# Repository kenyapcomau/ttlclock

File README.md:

# TTL clock

These are the Kicad design files for the TTL clock described in my [Hackaday project](https://hackaday.io/project/168157-ttl-binary-clock)

## Versioning

First release November 2019

## Notes

Due to the 2 LS load fan out of the CD4060 (U8), you should use a 74LS50 (U12) and not a standard TTL package, otherwise the 1 Hz signal will be unreliable. Anyway non-LS parts are rare these days. LS is lower power consumption too.

## Authors

* **Ken Yap**

## License

See the [LICENSE](LICENSE.md) file for license rights and limitations (MIT).

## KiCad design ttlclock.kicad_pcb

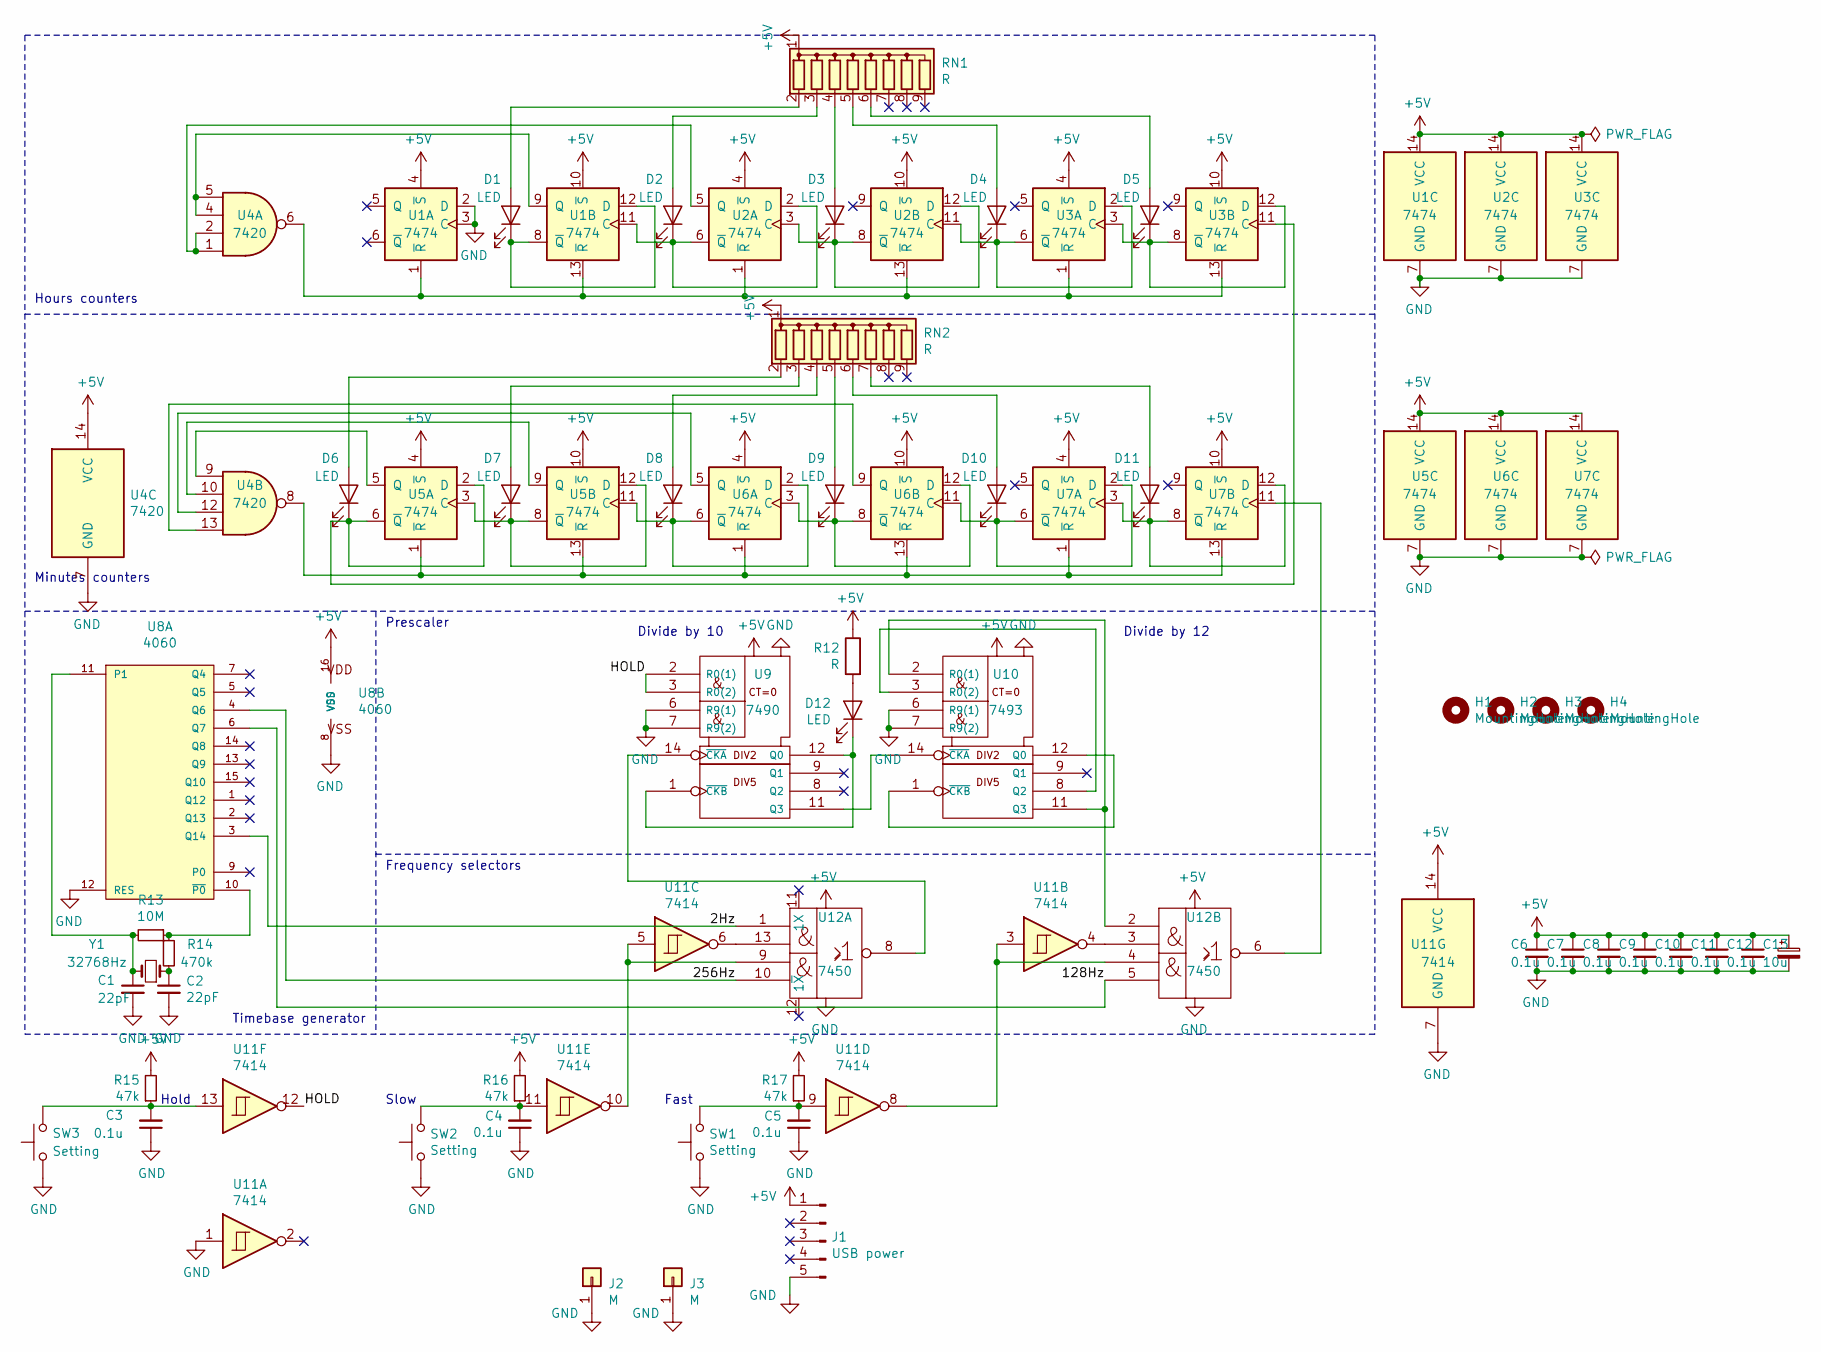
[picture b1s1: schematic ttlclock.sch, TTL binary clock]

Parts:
C1, C2: 22pF; C_Disc_D3.0mm_W1.6mm_P2.50mm
C3, C4, C5, C6, C7, C8, C9, C10, C11, C12: 0.1u; C_Rect_L7.2mm_W2.5mm_P5.00mm_FKS2_FKP2_MKS2_MKP2
C13: 10u; CP_Radial_D6.3mm_P2.50mm
D1, D2, D3, D4, D5, D6, D7, D8, D9, D10, D11, D12: LED; LED_D3.0mm
H1, H2, H3, H4: MountingHole; MountingHole_3.5mm_Pad
J1: USB power; PinHeader_1x05_P2.54mm_Vertical
J2, J3: M; PinHeader_1x01_P2.54mm_Vertical
R12: R; R_Axial_DIN0207_L6.3mm_D2.5mm_P10.16mm_Horizontal
R13: 10M; R_Axial_DIN0207_L6.3mm_D2.5mm_P10.16mm_Horizontal
R14: 470k; R_Axial_DIN0207_L6.3mm_D2.5mm_P10.16mm_Horizontal
R15, R16, R17: 47k; R_Axial_DIN0207_L6.3mm_D2.5mm_P10.16mm_Horizontal
RN1, RN2: R; R_Array_SIP9
SW1, SW2, SW3: Setting; SW_PUSH_6mm_H4.3mm
U1, U2, U3, U5, U6, U7: 7474; DIP-14_W7.62mm_LongPads
U4: 7420; DIP-14_W7.62mm_LongPads
U8: 4060; DIP-16_W7.62mm_LongPads
U9: 7490; DIP-14_W7.62mm_LongPads
U10: 7493; DIP-14_W7.62mm_LongPads
U11: 7414; DIP-14_W7.62mm_LongPads
U12: 7450; DIP-14_W7.62mm_LongPads
Y1: 32768Hz; Crystal_C38-LF_D3.0mm_L8.0mm_Horizontal

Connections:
+5V: C6.1, C7.1, C8.1, C9.1, C10.1, C11.1, C12.1, C13.1, J1.1, R12.1, R15.2, R16.2, R17.2, RN1.1 (common), RN2.1 (common), U1.4 (~S), U1.10 (~S), U1.14 (VCC), U2.4 (~S), U2.10 (~S), U2.14 (VCC), U3.4 (~S), U3.10 (~S), U3.14 (VCC), U4.14 (VCC), U5.4 (~S), U5.10 (~S), U5.14 (VCC), U6.4 (~S), U6.10 (~S), U6.14 (VCC), U7.4 (~S), U7.10 (~S), U7.14 (VCC), U8.16 (VDD), U9.5 (VCC), U10.5 (VCC), U11.14 (VCC), U12.14 (VCC)
/2Hz: U8.3 (Q14), U12.1
/128Hz: U8.6 (Q7), U12.5
/256Hz: U8.4 (Q6), U12.10
/HOLD: U9.2 (R0(1)), U9.3 (R0(2)), U11.12
GND: C1.2, C2.2, C3.1, C4.1, C5.1, C6.2, C7.2, C8.2, C9.2, C10.2, C11.2, C12.2, C13.2, J1.5, J2.1, J3.1, SW1.1, SW2.1, SW3.1, U1.2 (D), U1.3 (C), U1.7 (GND), U2.7 (GND), U3.7 (GND), U4.7 (GND), U5.7 (GND), U6.7 (GND), U7.7 (GND), U8.8 (VSS), U8.12 (RES), U9.6 (R9(1)), U9.7 (R9(2)), U9.10 (GND), U10.6 (R9(1)), U10.7 (R9(2)), U10.10 (GND), U11.1, U11.7 (GND), U12.7 (GND)
unnamed: C1.1, R13.2, U8.11 (P1), Y1.2
unnamed: C2.1, R14.2, Y1.1
unnamed: C3.2, R15.1, SW3.2, U11.13
unnamed: C4.2, R16.1, SW2.2, U11.11
unnamed: C5.2, R17.1, SW1.2, U11.9
unnamed: D1.1 (K), U1.8 (~Q), U1.12 (D)
unnamed: D1.2 (A), RN1.2 (R1)
unnamed: D2.1 (K), U1.11 (C), U2.2 (D), U2.6 (~Q)
unnamed: D2.2 (A), RN1.3 (R2)
unnamed: D3.1 (K), U2.3 (C), U2.8 (~Q), U2.12 (D)
unnamed: D3.2 (A), RN1.4 (R3)
unnamed: D4.1 (K), U2.11 (C), U3.2 (D), U3.6 (~Q)
unnamed: D4.2 (A), RN1.5 (R4)
unnamed: D5.1 (K), U3.3 (C), U3.8 (~Q), U3.12 (D)
unnamed: D5.2 (A), RN1.6 (R5)
unnamed: D6.1 (K), U3.11 (C), U5.2 (D), U5.6 (~Q)
unnamed: D6.2 (A), RN2.2 (R1)
unnamed: D7.1 (K), U5.3 (C), U5.8 (~Q), U5.12 (D)
unnamed: D7.2 (A), RN2.3 (R2)
unnamed: D8.1 (K), U5.11 (C), U6.2 (D), U6.6 (~Q)
unnamed: D8.2 (A), RN2.4 (R3)
unnamed: D9.1 (K), U6.3 (C), U6.8 (~Q), U6.12 (D)
unnamed: D9.2 (A), RN2.5 (R4)
unnamed: D10.1 (K), U6.11 (C), U7.2 (D), U7.6 (~Q)
unnamed: D10.2 (A), RN2.6 (R5)
unnamed: D11.1 (K), U7.3 (C), U7.8 (~Q), U7.12 (D)
unnamed: D11.2 (A), RN2.7 (R6)
unnamed: D12.1 (K), U9.1 (~CKB), U9.12 (Q0)
unnamed: D12.2 (A), R12.2
unnamed: R13.1, R14.1, U8.10 (~P0~)
unnamed: U1.1 (~R), U1.13 (~R), U2.1 (~R), U2.13 (~R), U3.1 (~R), U3.13 (~R), U4.6
unnamed: U1.9 (Q), U4.4, U4.5
unnamed: U2.5 (Q), U4.1, U4.2
unnamed: U4.8, U5.1 (~R), U5.13 (~R), U6.1 (~R), U6.13 (~R), U7.1 (~R), U7.13 (~R)
unnamed: U4.9, U5.5 (Q)
unnamed: U4.10, U5.9 (Q)
unnamed: U4.12, U6.5 (Q)
unnamed: U4.13, U6.9 (Q)
unnamed: U10.1 (~CKB), U10.12 (Q0)
unnamed: U10.3 (R0(2)), U10.8 (Q2)
unnamed: U10.2 (R0(1)), U10.11 (Q3), U12.2
unnamed: U9.11 (Q3), U10.14 (~CKA)
unnamed: U11.3, U11.8, U12.4
unnamed: U11.4, U12.3
unnamed: U11.6, U12.13
unnamed: U11.5, U11.10, U12.9
unnamed: U7.11 (C), U12.6
unnamed: U9.14 (~CKA), U12.8

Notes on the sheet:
Slow
Fast
Hold
Hours counters
Minutes counters
Timebase generator
Frequency selectors
Prescaler
Divide by 10
Divide by 12

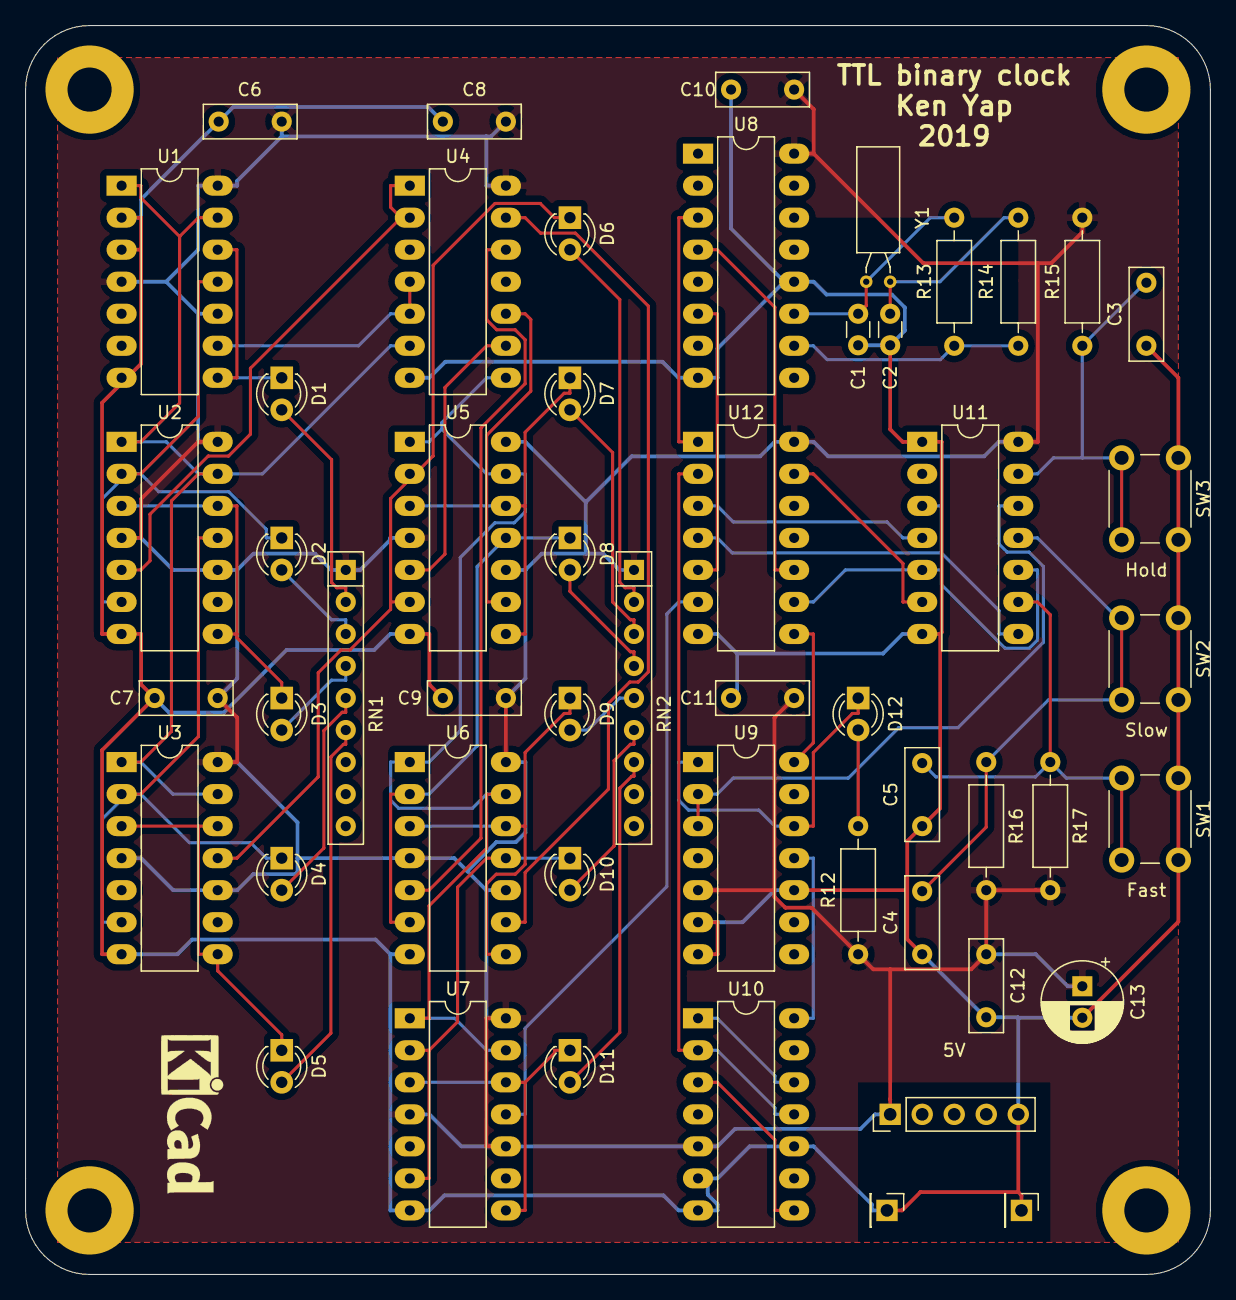
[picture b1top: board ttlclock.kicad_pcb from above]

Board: 2 copper layers, 94.0 x 99.1 mm, 58 parts (1 on the bottom side), 54 nets.

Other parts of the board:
K1, K2: KiCad-Logo_5mm_SilkScreen

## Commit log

2019-10-30 First release
2019-10-30 Add link to Hackaday project page
2019-10-30 Fix markdown syntax
2019-11-18 Note about using 74LS50
